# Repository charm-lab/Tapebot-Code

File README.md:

# Tapebot-Code
Code to control Tapebot

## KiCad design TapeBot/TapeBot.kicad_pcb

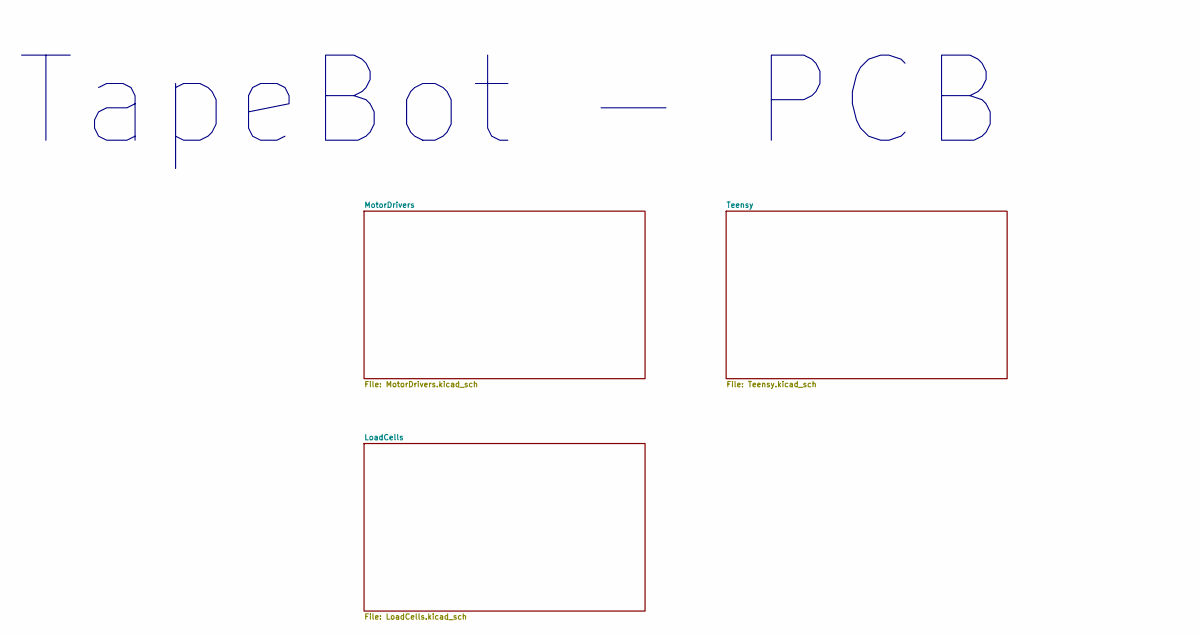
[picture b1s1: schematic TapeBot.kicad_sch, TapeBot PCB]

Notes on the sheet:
TapeBot - PCB

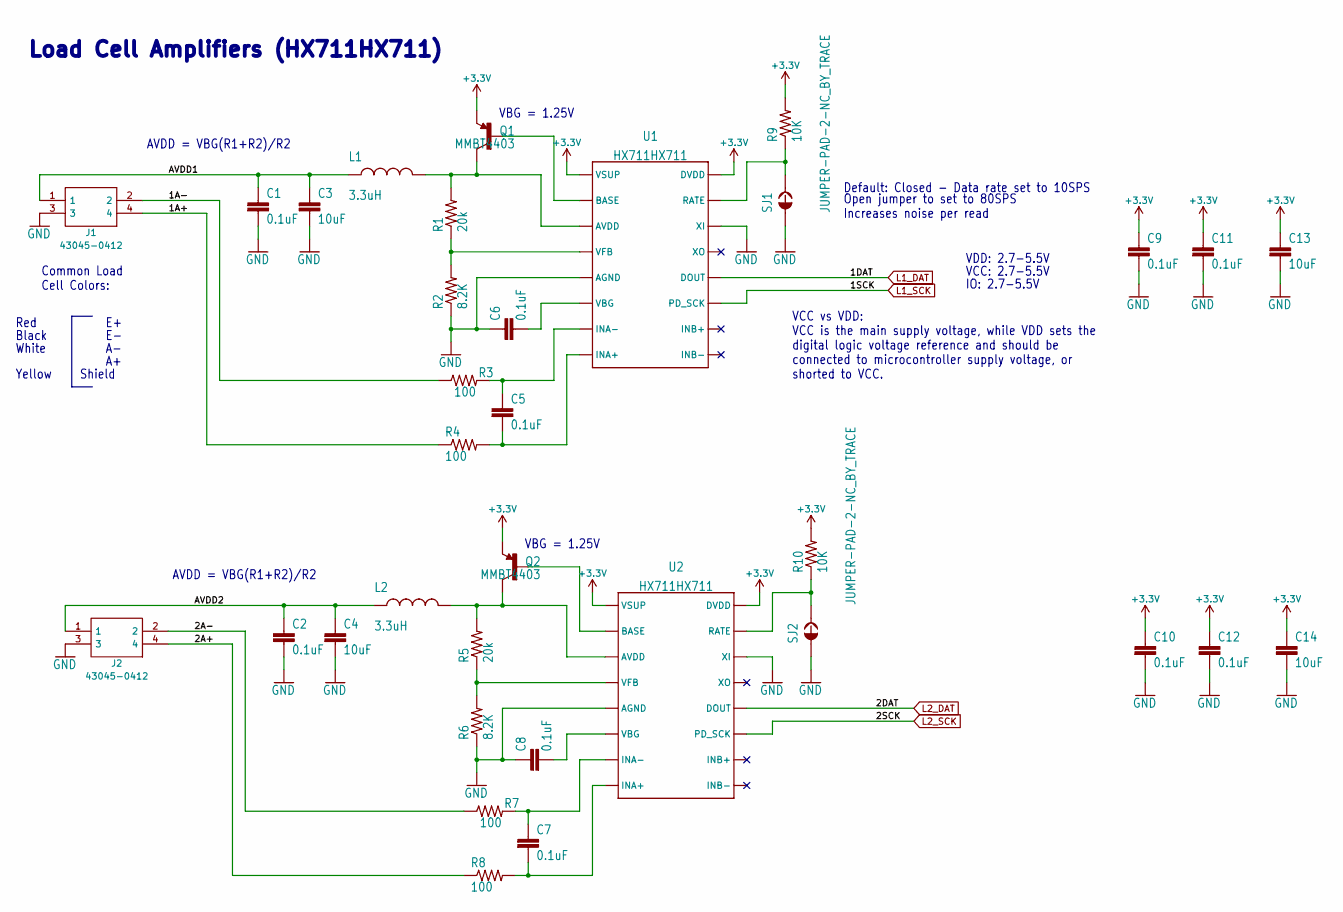
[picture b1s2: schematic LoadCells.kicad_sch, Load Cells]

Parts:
C1: 0.1uF; C_0603_1608Metric
C2, C5, C6, C7, C8, C9, C10, C11, C12: 0.1uF; C_0603_1608Metric_Pad1.08x0.95mm_HandSolder
C3, C4, C13, C14: 10uF; C_0805_2012Metric_Pad1.18x1.45mm_HandSolder
J1, J2: 43045-0412; 43045-04YY_121314; Mouser Part Number 538-43045-0412
L1, L2: 3.3uH; C_0805_2012Metric_Pad1.18x1.45mm_HandSolder
Q1, Q2: MMBT4403; SOT23-BEC
R1, R5: 20k; C_0603_1608Metric_Pad1.08x0.95mm_HandSolder
R2, R6: 8.2K; C_0603_1608Metric_Pad1.08x0.95mm_HandSolder
R3, R4, R7, R8: 100; C_0603_1608Metric_Pad1.08x0.95mm_HandSolder
R9, R10: 10K; C_0603_1608Metric_Pad1.08x0.95mm_HandSolder
SJ1, SJ2: JUMPER-PAD-2-NC_BY_TRACE; SolderJumper-2_P1.3mm_Open_TrianglePad1.0x1.5mm
U1, U2: HX711HX711; SOP127P600X180-16N

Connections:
+3.3V: C9.1, C10.1, C11.1, C12.1, C13.1, C14.1, Q1.E, Q2.E, R9.2, R10.2, U1.1 (VSUP), U1.16 (DVDD), U2.1 (VSUP), U2.16 (DVDD); also elsewhere on the board
/LoadCells/1A+: J1.4, R4.1
/LoadCells/1A-: J1.2, R3.1
/LoadCells/2A+: J2.4, R8.1
/LoadCells/2A-: J2.2, R7.1
/LoadCells/AVDD1: C1.1, C3.1, J1.1, L1.1
/LoadCells/AVDD2: C2.1, C4.1, J2.1, L2.1
GND: C1.2, C2.2, C3.2, C4.2, C6.1, C8.1, C9.2, C10.2, C11.2, C12.2, C13.2, C14.2, J1.3, J2.3, R2.1, R6.1, SJ1.1, SJ2.1, U1.5 (AGND), U1.14 (XI), U2.5 (AGND), U2.14 (XI); also elsewhere on the board
L1_DAT: U1.12 (DOUT); also elsewhere on the board
L1_SCK: U1.11 (PD_SCK); also elsewhere on the board
L2_DAT: U2.12 (DOUT); also elsewhere on the board
L2_SCK: U2.11 (PD_SCK); also elsewhere on the board
unnamed: C5.1, R3.2, U1.7 (INA-)
unnamed: C5.2, R4.2, U1.8 (INA+)
unnamed: C6.2, U1.6 (VBG)
unnamed: C7.1, R7.2, U2.7 (INA-)
unnamed: C7.2, R8.2, U2.8 (INA+)
unnamed: C8.2, U2.6 (VBG)
unnamed: L1.2, Q1.C, R1.2, U1.3 (AVDD)
unnamed: L2.2, Q2.C, R5.2, U2.3 (AVDD)
unnamed: Q1.B, U1.2 (BASE)
unnamed: Q2.B, U2.2 (BASE)
unnamed: R1.1, R2.2, U1.4 (VFB)
unnamed: R5.1, R6.2, U2.4 (VFB)
unnamed: R9.1, SJ1.2, U1.15 (RATE)
unnamed: R10.1, SJ2.2, U2.15 (RATE)

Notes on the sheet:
White
VBG = 1.25V
Shield
Yellow
Black
VDD: 2.7-5.5V
Load Cell Amplifiers (HX711HX711)
Common Load Cell Colors:
VCC vs VDD: VCC is the main supply voltage, while VDD sets the digital logic voltage reference and should be connected to microcontroller supply voltage, or shorted to VCC.
VCC: 2.7-5.5V
AVDD = VBG(R1+R2)/R2
Red
Default: Closed - Data rate set to 10SPS
Open jumper to set to 80SPS Increases noise per read
IO: 2.7-5.5V

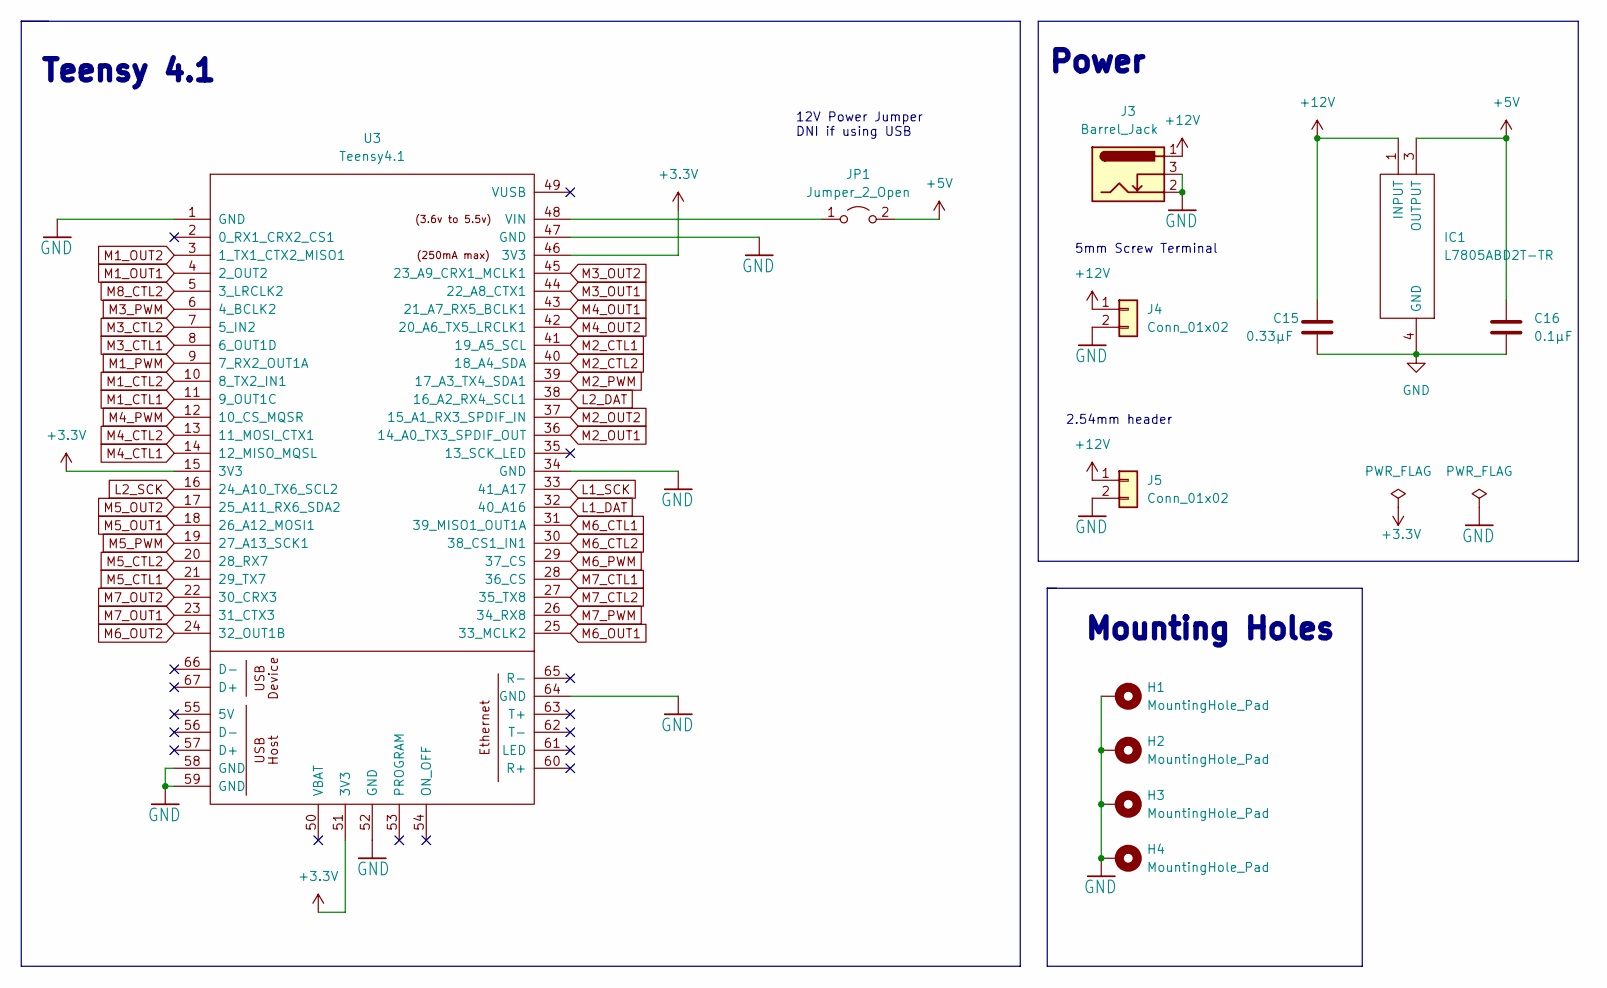
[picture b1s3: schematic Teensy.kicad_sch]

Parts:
C15: 0.33µF; C_0805_2012Metric_Pad1.18x1.45mm_HandSolder
C16: 0.1µF; C_0805_2012Metric_Pad1.18x1.45mm_HandSolder
H1, H2, H3, H4: MountingHole_Pad; MountingHole_4.3mm_M4_DIN965_Pad
IC1: L7805ABD2T-TR; D2PAK-STB35NF10T4; Mouser Part Number 511-L7805ABD2T-TR
J3: Barrel_Jack; BarrelJack_GCT_DCJ200-10-A_Horizontal
J4: Conn_01x02; TE_282837-2
J5: Conn_01x02; PinHeader_1x02_P2.54mm_Vertical
JP1: Jumper_2_Open; PinHeader_1x02_P2.54mm_Vertical
U3: Teensy4.1; Teensy41

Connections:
+3.3V: U3.15 (3V3), U3.46 (3V3), U3.51 (3V3); also elsewhere on the board
+5V: C16.1, IC1.3 (OUTPUT), JP1.2 (B)
+12V: C15.1, IC1.1 (INPUT), J3.1, J4.1, J5.1; also elsewhere on the board
GND: C15.2, C16.2, H1.1, H2.1, H3.1, H4.1, IC1.4 (GND), J3.2, J3.3, J4.2, J5.2, U3.1 (GND), U3.34 (GND), U3.47 (GND), U3.52 (GND), U3.58 (GND), U3.59 (GND), U3.64 (GND); also elsewhere on the board
L1_DAT: U3.32 (40_A16); also elsewhere on the board
L1_SCK: U3.33 (41_A17); also elsewhere on the board
L2_DAT: U3.38 (16_A2_RX4_SCL1); also elsewhere on the board
L2_SCK: U3.16 (24_A10_TX6_SCL2); also elsewhere on the board
M1_CTL1: U3.11 (9_OUT1C); also elsewhere on the board
M1_CTL2: U3.10 (8_TX2_IN1); also elsewhere on the board
M1_OUT1: U3.4 (2_OUT2); also elsewhere on the board
M1_OUT2: U3.3 (1_TX1_CTX2_MISO1); also elsewhere on the board
M1_PWM: U3.9 (7_RX2_OUT1A); also elsewhere on the board
M2_CTL1: U3.41 (19_A5_SCL); also elsewhere on the board
M2_CTL2: U3.40 (18_A4_SDA); also elsewhere on the board
M2_OUT1: U3.36 (14_A0_TX3_SPDIF_OUT); also elsewhere on the board
M2_OUT2: U3.37 (15_A1_RX3_SPDIF_IN); also elsewhere on the board
M2_PWM: U3.39 (17_A3_TX4_SDA1); also elsewhere on the board
M3_CTL1: U3.8 (6_OUT1D); also elsewhere on the board
M3_CTL2: U3.7 (5_IN2); also elsewhere on the board
M3_OUT1: U3.44 (22_A8_CTX1); also elsewhere on the board
M3_OUT2: U3.45 (23_A9_CRX1_MCLK1); also elsewhere on the board
M3_PWM: U3.6 (4_BCLK2); also elsewhere on the board
M4_CTL1: U3.14 (12_MISO_MQSL); also elsewhere on the board
M4_CTL2: U3.13 (11_MOSI_CTX1); also elsewhere on the board
M4_OUT1: U3.43 (21_A7_RX5_BCLK1); also elsewhere on the board
M4_OUT2: U3.42 (20_A6_TX5_LRCLK1); also elsewhere on the board
M4_PWM: U3.12 (10_CS_MQSR); also elsewhere on the board
M5_CTL1: U3.21 (29_TX7); also elsewhere on the board
M5_CTL2: U3.20 (28_RX7); also elsewhere on the board
M5_OUT1: U3.18 (26_A12_MOSI1); also elsewhere on the board
M5_OUT2: U3.17 (25_A11_RX6_SDA2); also elsewhere on the board
M5_PWM: U3.19 (27_A13_SCK1); also elsewhere on the board
M6_CTL1: U3.31 (39_MISO1_OUT1A); also elsewhere on the board
M6_CTL2: U3.30 (38_CS1_IN1); also elsewhere on the board
M6_OUT1: U3.25 (33_MCLK2); also elsewhere on the board
M6_OUT2: U3.24 (32_OUT1B); also elsewhere on the board
M6_PWM: U3.29 (37_CS); also elsewhere on the board
M7_CTL1: U3.28 (36_CS); also elsewhere on the board
M7_CTL2: U3.27 (35_TX8); also elsewhere on the board
M7_OUT1: U3.23 (31_CTX3); also elsewhere on the board
M7_OUT2: U3.22 (30_CRX3); also elsewhere on the board
M7_PWM: U3.26 (34_RX8); also elsewhere on the board
M8_CTL2: U3.5 (3_LRCLK2)
unnamed: JP1.1 (A), U3.48 (VIN)

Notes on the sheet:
5mm Screw Terminal
12V Power Jumper DNI if using USB
2.54mm header
Teensy 4.1
Power
Mounting Holes

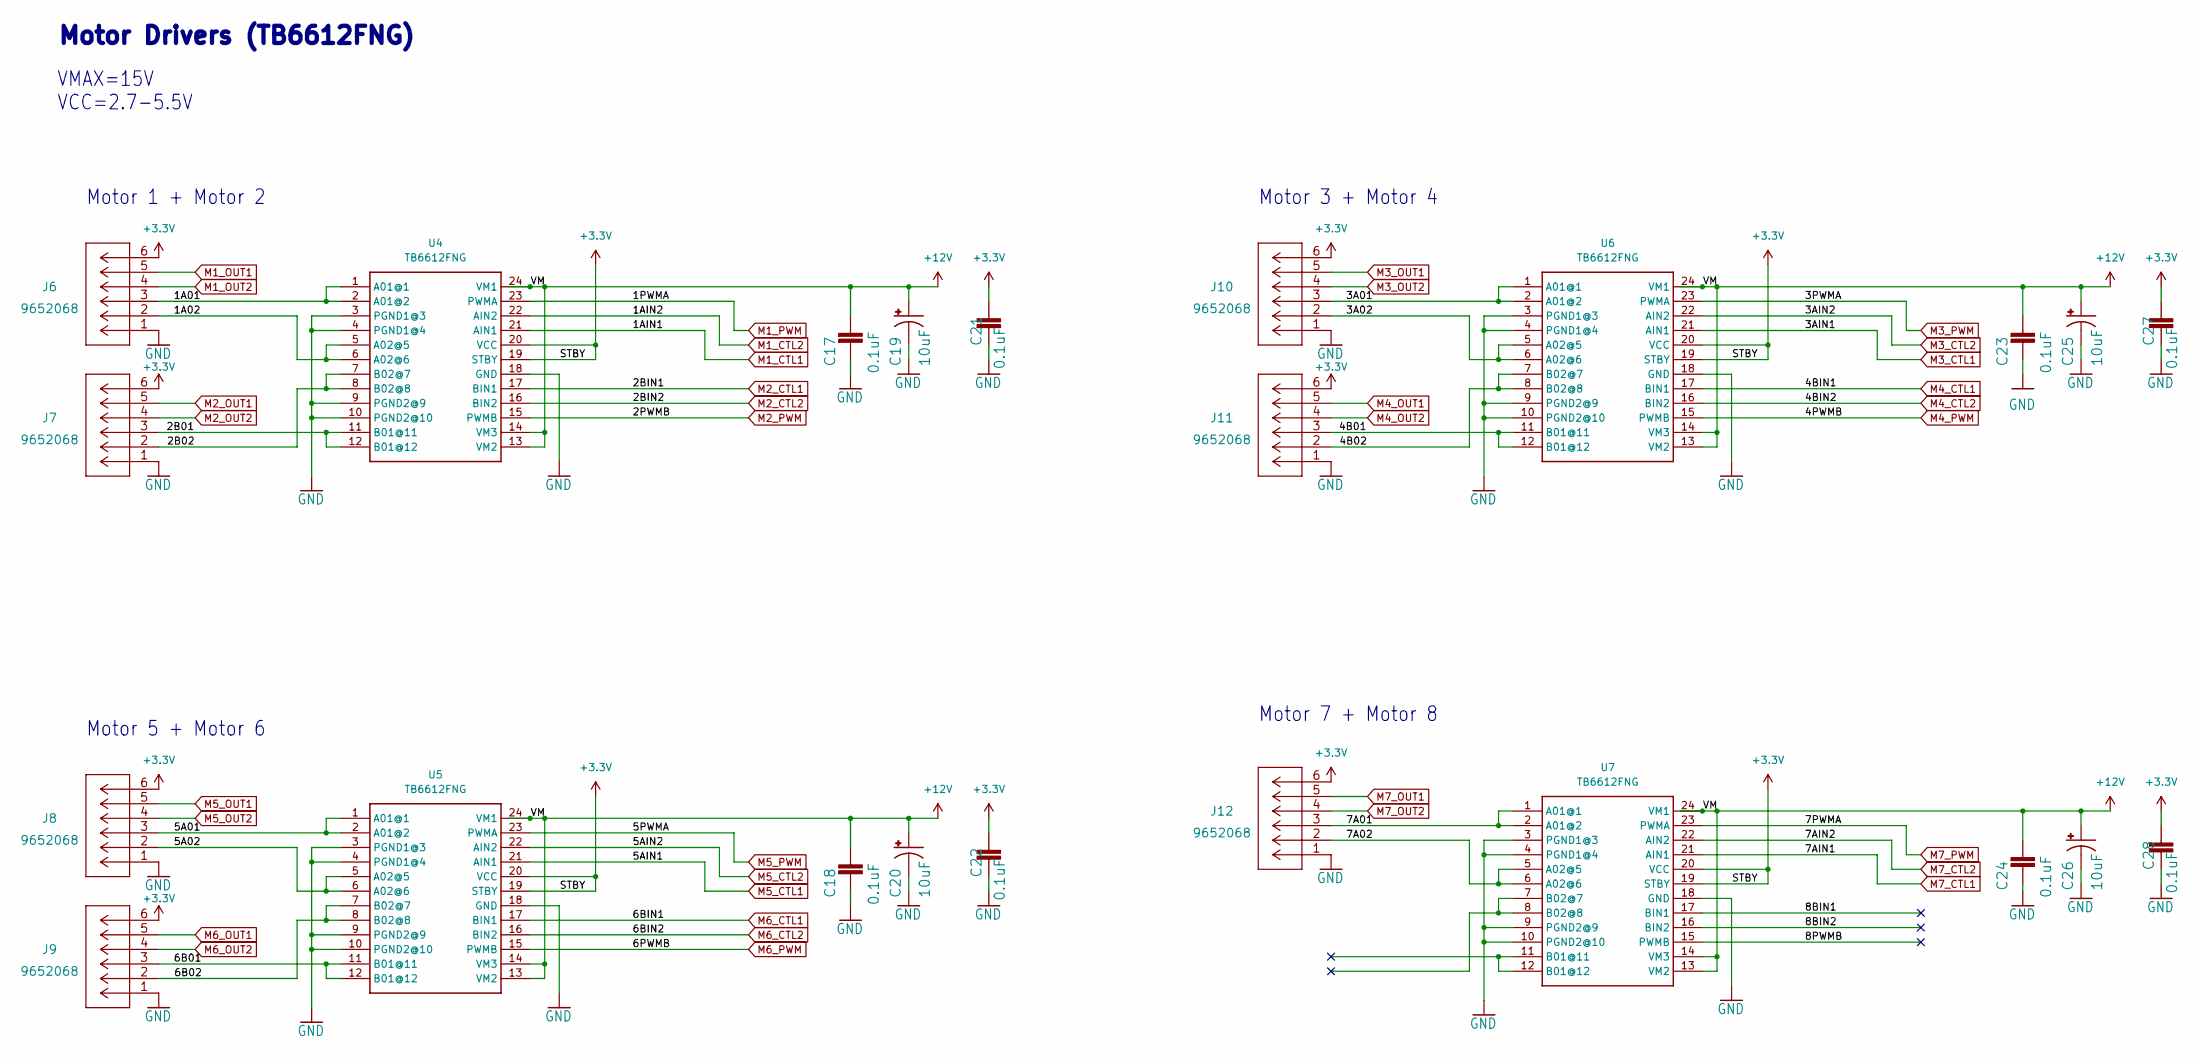
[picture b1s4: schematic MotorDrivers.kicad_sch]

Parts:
C17, C18, C21, C22, C23, C24, C27, C28: 0.1uF; C_0603_1608Metric_Pad1.08x0.95mm_HandSolder
C19, C20, C25, C26: 10uF; CAPPM6032X280N
J6, J7, J8, J9, J10, J11, J12: 9652068
U4, U5, U6, U7: TB6612FNG; SOP65P760X160-24N

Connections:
+3.3V: C21.1, C22.1, C27.1, C28.1, J6.6, J7.6, J8.6, J9.6, J10.6, J11.6, J12.6, U4.19 (STBY), U4.20 (VCC), U5.19 (STBY), U5.20 (VCC), U6.19 (STBY), U6.20 (VCC), U7.19 (STBY), U7.20 (VCC); also elsewhere on the board
+12V: C17.1, C18.1, C19.A (+), C20.A (+), C23.1, C24.1, C25.A (+), C26.A (+), U4.13 (VM2), U4.14 (VM3), U4.24 (VM1), U5.13 (VM2), U5.14 (VM3), U5.24 (VM1), U6.13 (VM2), U6.14 (VM3), U6.24 (VM1), U7.13 (VM2), U7.14 (VM3), U7.24 (VM1); also elsewhere on the board
/MotorDrivers/1A01: J6.3, U4.1 (A01@1), U4.2 (A01@2)
/MotorDrivers/1A02: J6.2, U4.5 (A02@5), U4.6 (A02@6)
/MotorDrivers/2B01: J7.3, U4.11 (B01@11), U4.12 (B01@12)
/MotorDrivers/2B02: J7.2, U4.7 (B02@7), U4.8 (B02@8)
/MotorDrivers/3A01: J10.3, U6.1 (A01@1), U6.2 (A01@2)
/MotorDrivers/3A02: J10.2, U6.5 (A02@5), U6.6 (A02@6)
/MotorDrivers/4B01: J11.3, U6.11 (B01@11), U6.12 (B01@12)
/MotorDrivers/4B02: J11.2, U6.7 (B02@7), U6.8 (B02@8)
/MotorDrivers/5A01: J8.3, U5.1 (A01@1), U5.2 (A01@2)
/MotorDrivers/5A02: J8.2, U5.5 (A02@5), U5.6 (A02@6)
/MotorDrivers/6B01: J9.3, U5.11 (B01@11), U5.12 (B01@12)
/MotorDrivers/6B02: J9.2, U5.7 (B02@7), U5.8 (B02@8)
/MotorDrivers/7A01: J12.3, U7.1 (A01@1), U7.2 (A01@2)
/MotorDrivers/7A02: J12.2, U7.5 (A02@5), U7.6 (A02@6)
/MotorDrivers/8BIN1: U7.17 (BIN1)
/MotorDrivers/8BIN2: U7.16 (BIN2)
/MotorDrivers/8PWMB: U7.15 (PWMB)
GND: C17.2, C18.2, C19.C (-), C20.C (-), C21.2, C22.2, C23.2, C24.2, C25.C (-), C26.C (-), C27.2, C28.2, J6.1, J7.1, J8.1, J9.1, J10.1, J11.1, J12.1, U4.3 (PGND1@3), U4.4 (PGND1@4), U4.9 (PGND2@9), U4.10 (PGND2@10), U4.18 (GND), U5.3 (PGND1@3), U5.4 (PGND1@4), U5.9 (PGND2@9), U5.10 (PGND2@10), U5.18 (GND), U6.3 (PGND1@3), U6.4 (PGND1@4), U6.9 (PGND2@9), U6.10 (PGND2@10), U6.18 (GND), U7.3 (PGND1@3), U7.4 (PGND1@4), U7.9 (PGND2@9), U7.10 (PGND2@10), U7.18 (GND); also elsewhere on the board
M1_CTL1: U4.21 (AIN1); also elsewhere on the board
M1_CTL2: U4.22 (AIN2); also elsewhere on the board
M1_OUT1: J6.5; also elsewhere on the board
M1_OUT2: J6.4; also elsewhere on the board
M1_PWM: U4.23 (PWMA); also elsewhere on the board
M2_CTL1: U4.17 (BIN1); also elsewhere on the board
M2_CTL2: U4.16 (BIN2); also elsewhere on the board
M2_OUT1: J7.5; also elsewhere on the board
M2_OUT2: J7.4; also elsewhere on the board
M2_PWM: U4.15 (PWMB); also elsewhere on the board
M3_CTL1: U6.21 (AIN1); also elsewhere on the board
M3_CTL2: U6.22 (AIN2); also elsewhere on the board
M3_OUT1: J10.5; also elsewhere on the board
M3_OUT2: J10.4; also elsewhere on the board
M3_PWM: U6.23 (PWMA); also elsewhere on the board
M4_CTL1: U6.17 (BIN1); also elsewhere on the board
M4_CTL2: U6.16 (BIN2); also elsewhere on the board
M4_OUT1: J11.5; also elsewhere on the board
M4_OUT2: J11.4; also elsewhere on the board
M4_PWM: U6.15 (PWMB); also elsewhere on the board
M5_CTL1: U5.21 (AIN1); also elsewhere on the board
M5_CTL2: U5.22 (AIN2); also elsewhere on the board
M5_OUT1: J8.5; also elsewhere on the board
M5_OUT2: J8.4; also elsewhere on the board
M5_PWM: U5.23 (PWMA); also elsewhere on the board
M6_CTL1: U5.17 (BIN1); also elsewhere on the board
M6_CTL2: U5.16 (BIN2); also elsewhere on the board
M6_OUT1: J9.5; also elsewhere on the board
M6_OUT2: J9.4; also elsewhere on the board
M6_PWM: U5.15 (PWMB); also elsewhere on the board
M7_CTL1: U7.21 (AIN1); also elsewhere on the board
M7_CTL2: U7.22 (AIN2); also elsewhere on the board
M7_OUT1: J12.5; also elsewhere on the board
M7_OUT2: J12.4; also elsewhere on the board
M7_PWM: U7.23 (PWMA); also elsewhere on the board

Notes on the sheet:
VMAX=15V VCC=2.7-5.5V
Motor 7 + Motor 8
Motor 5 + Motor 6
Motor 3 + Motor 4
Motor Drivers (TB6612FNG)
Motor 1 + Motor 2

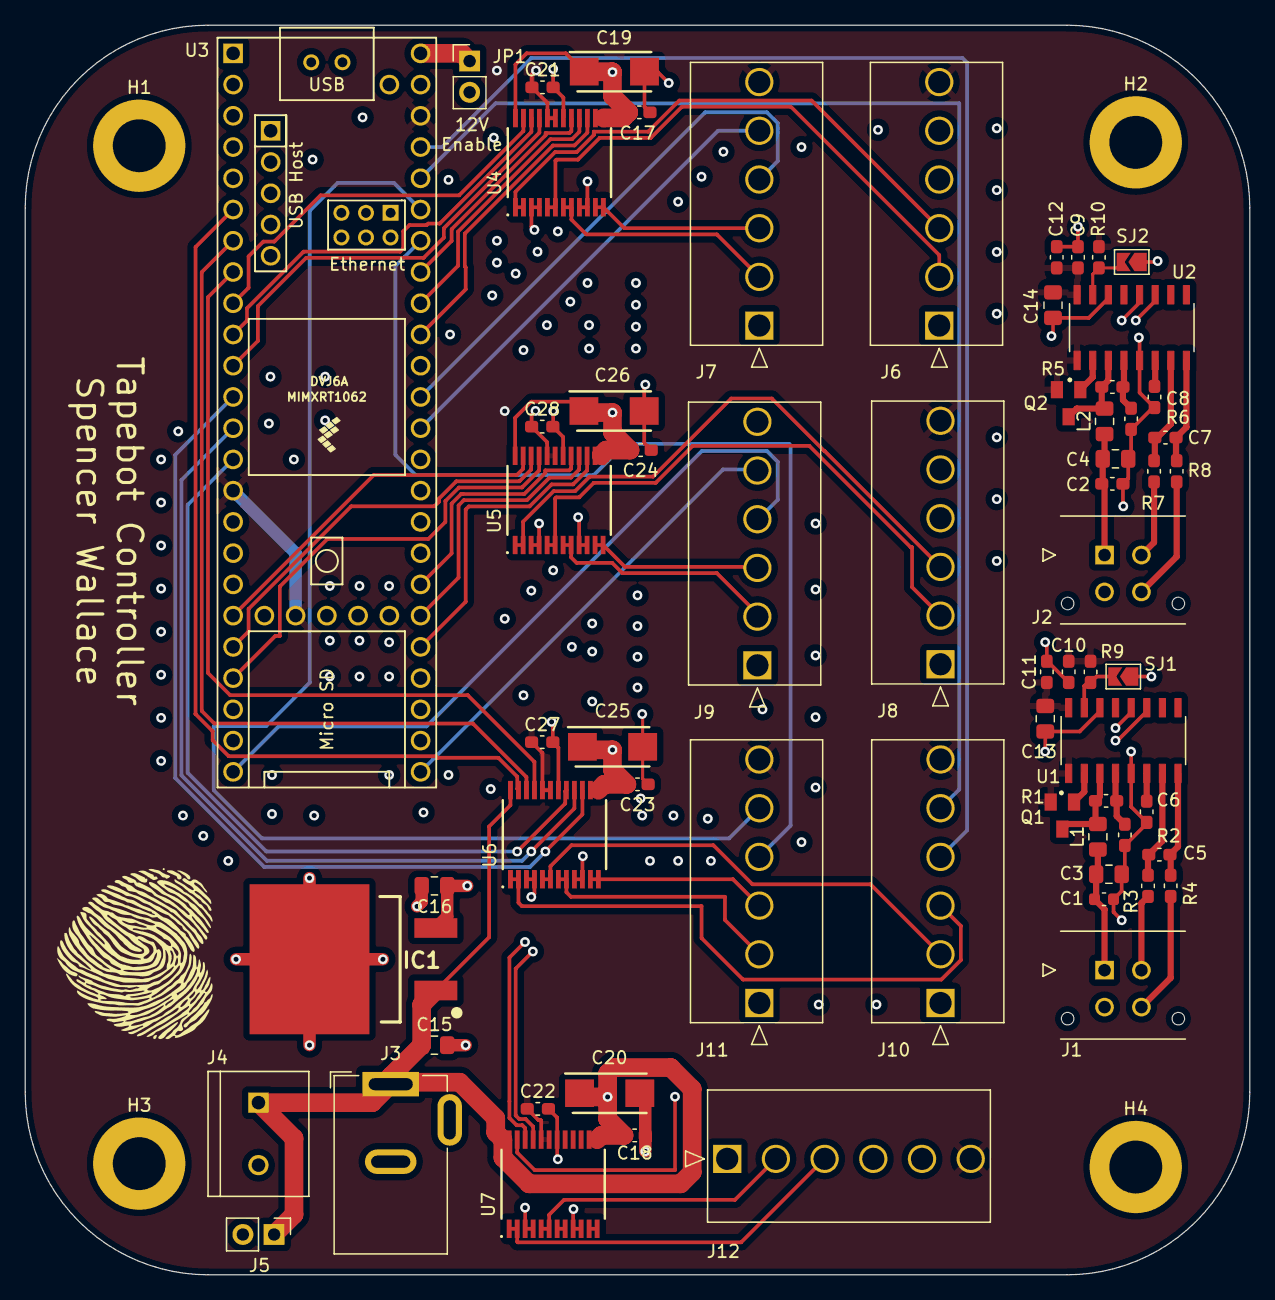
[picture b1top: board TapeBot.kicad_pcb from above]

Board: 4 copper layers, 99.6 x 101.6 mm, 69 parts (0 on the bottom side), 78 nets.

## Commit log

2023-01-20 Add Ryan Nguyen's most recent Tapebot control code from Fall 2022
2023-01-24 Added TapeBot PCB Files
2023-01-29 fixed footprints and symbols
2023-01-29 finished motor driver schematic and load cell schematic
2023-01-29 added label
2023-01-29 (mostly) finished schematic
2023-01-29 fixed footprints and 3d models
2023-02-07 arranged board
2023-02-14 First layout of PCB finished
2023-02-16 Fixed Voltage Regulator placement, Added ground vias
2023-02-16 Fixed some footprints
2023-02-16 Final Commit
2023-02-21 all edits
2023-04-03 Backup from Kicaid
2023-05-08 Updated pins
2023-05-09 Update main.cpp
    Specified that "Physical constants for rollers, spools, etc" in the code are in millimeters
2023-06-26 Uploaded the code for the setup
2023-07-11 Updated files with the recent changes to the system
2023-08-07 I updated all the filles and they are good to go for now
2023-10-06 I added a matlab script that calculates the moment vs bending angle
2024-10-02 My most recent changes to the code
2024-12-09 Scripts for experiment
2024-12-09 Reorganized and renamed files

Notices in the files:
parts and their libraries:
Copyright 2021 Accelerated Designs. All rights reserved.
